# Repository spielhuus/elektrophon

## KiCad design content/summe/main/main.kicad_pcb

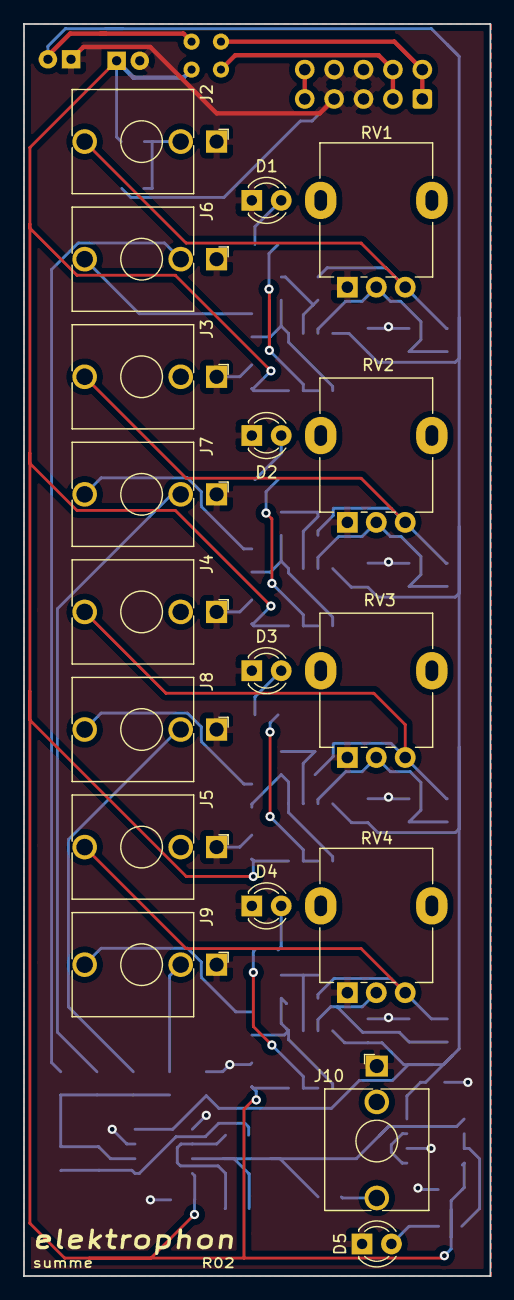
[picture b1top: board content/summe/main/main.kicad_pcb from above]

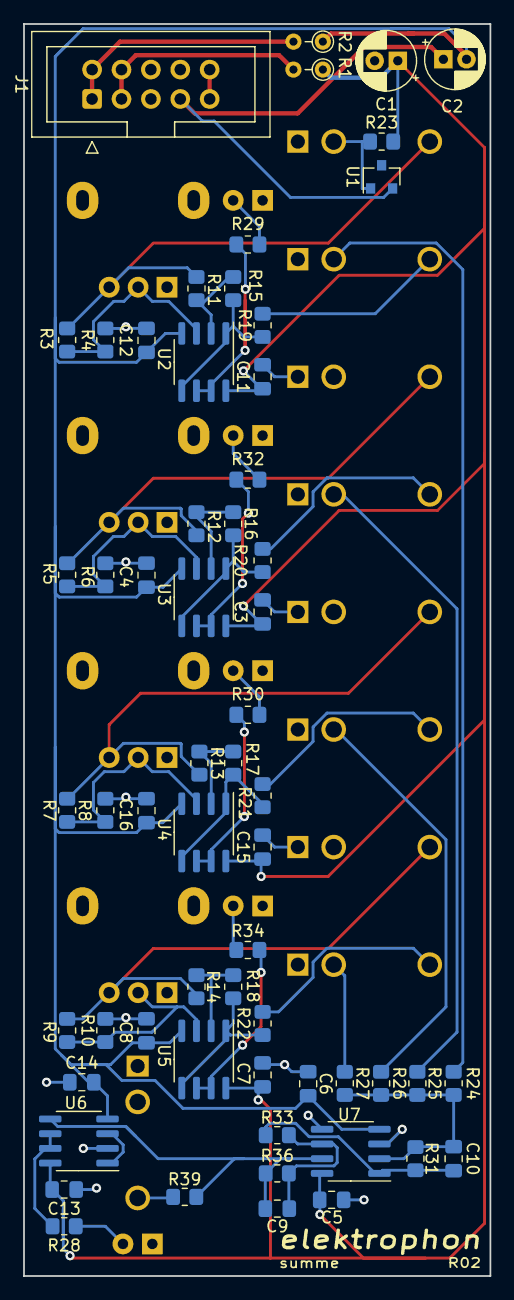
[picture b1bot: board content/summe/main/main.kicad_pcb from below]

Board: 2 copper layers, 40.3 x 108.2 mm, 78 parts (60 on the bottom side), 47 nets.

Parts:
C1, C2: 22u; CP_Radial_D5.0mm_P2.00mm
C3, C4, C5, C6, C7, C8, C11, C12, C13, C14, C15, C16: 0.1u; C_0805_2012Metric_Pad1.18x1.45mm_HandSolder
C9, C10: 100p; C_0805_2012Metric_Pad1.18x1.45mm_HandSolder
D1, D2, D3, D4: LED (Green/Yellow); LED_D3.0mm
D5: LED (Red/Yellow); LED_D3.0mm
J1: IDC Header; IDC-Header_2x05_P2.54mm_Vertical
J2, J3, J4, J5: IN; Jack_3.5mm_WQP-PJ398SM_Vertical
J6, J7, J8, J9, J10: OUT; Jack_3.5mm_WQP-PJ398SM_Vertical
R1, R2: 10; R_Axial_DIN0204_L3.6mm_D1.6mm_P2.54mm_Vertical
R3, R4, R5, R6, R7, R8, R9, R10: 47k; R_0805_2012Metric_Pad1.20x1.40mm_HandSolder
R11, R12, R13, R14, R15, R16, R17, R18, R24, R25, R26, R27, R31, R33, R36: 100k; R_0805_2012Metric_Pad1.20x1.40mm_HandSolder
R19, R20, R21, R22, R39: 1k; R_0805_2012Metric_Pad1.20x1.40mm_HandSolder
R23: 8.2k; R_0805_2012Metric_Pad1.20x1.40mm_HandSolder
R28, R29, R30, R32, R34: 500; R_0805_2012Metric_Pad1.20x1.40mm_HandSolder
RV1, RV2, RV3, RV4: 100k; Potentiometer_Alpha_RD901F-40-00D_Single_Vertical
U1: LM4040BIM3-5.0; SOT-23
U2, U3, U4, U5, U6, U7: TL072; SOIC-8_3.9x4.9mm_P1.27mm

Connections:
+5V: J1.9, J1.10
+15V: C1.1, C3.1, C5.1, C7.1, C11.1, C13.1, C15.1, R1.1, R23.2, U2.8, U3.8, U4.8, U5.8, U6.8, U7.8
-15V: C2.2, C4.2, C6.2, C8.2, C12.2, C14.2, C16.2, R2.1, U2.4, U3.4, U4.4, U5.4, U6.4, U7.4
/IN_1: R15.1, R19.1, U2.1, U2.5
/IN_2: R16.1, R20.1, U3.1, U3.5
/IN_3: R17.1, R21.1, U4.1, U4.5
/IN_4: R18.1, R22.1, U5.1, U5.5
/MIX_1: J6.TN, R24.1
/MIX_2: J7.TN, R25.1
/MIX_3: J8.TN, R26.1
/MIX_4: J9.TN, R27.1
/OUT: C9.1, R36.2, R39.1, U6.5, U7.7
/REF: J2.TN, R23.1, U1.1
GND: C1.2, C2.1, C3.2, C4.1, C5.2, C6.1, C7.2, C8.1, C11.2, C12.1, C13.2, C14.1, C15.2, C16.1, D1.1, D2.1, D3.1, D4.1, D5.1, J1.5, J1.6, J1.7, J1.8, J2.S, J3.S, J4.S, J5.S, J6.S, J7.S, J8.S, J9.S, J10.S, R4.2, R6.2, R8.2, R10.2, RV1.1, RV2.1, RV3.1, RV4.1, U1.2, U6.2, U7.3, U7.5
unnamed: C9.2, R33.2, R36.1, U7.6
unnamed: C10.1, R31.2, R33.1, U7.1
unnamed: C10.2, R24.2, R25.2, R26.2, R27.2, R31.1, U7.2
unnamed: D1.2, R29.1
unnamed: D2.2, R32.1
unnamed: D3.2, R30.1
unnamed: D4.2, R34.1
unnamed: D5.2, R28.1
unnamed: J2.T, R3.1, R11.2, RV1.3
unnamed: J3.T, R5.1, R12.2, RV2.3
unnamed: J4.T, R7.1, R13.2, RV3.3
unnamed: J5.T, R9.1, R14.2, RV4.3
unnamed: J6.T, R19.2
unnamed: J7.T, R20.2
unnamed: J8.T, R21.2
unnamed: J9.T, R22.2
unnamed: J10.T, R39.2
unnamed: R3.2, R4.1, RV1.2, U2.3
unnamed: R5.2, R6.1, RV2.2, U3.3
unnamed: R7.2, R8.1, RV3.2, U4.3
unnamed: R9.2, R10.1, RV4.2, U5.3
unnamed: R11.1, R15.2, U2.2
unnamed: R12.1, R16.2, U3.2
unnamed: R13.1, R17.2, U4.2
unnamed: R14.1, R18.2, U5.2
unnamed: R28.2, U6.6, U6.7
unnamed: R29.2, U2.6, U2.7
unnamed: R30.2, U4.6, U4.7
unnamed: R32.2, U3.6, U3.7
unnamed: R34.2, U5.6, U5.7
unnamed: U6.1, U6.3
VN: J1.1, J1.2, R2.2
VP: J1.3, J1.4, R1.2

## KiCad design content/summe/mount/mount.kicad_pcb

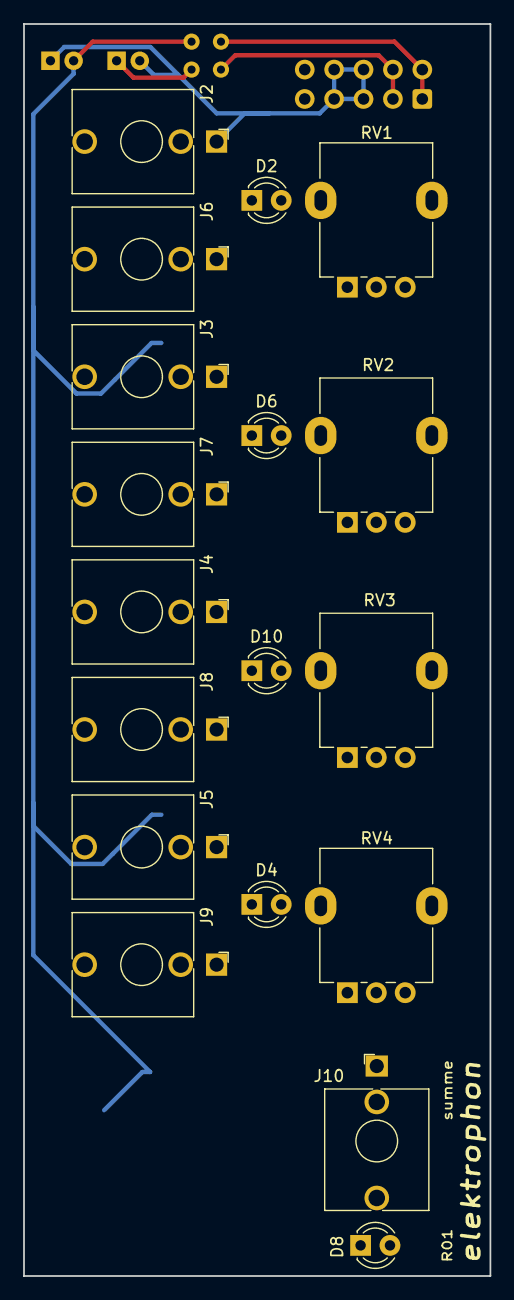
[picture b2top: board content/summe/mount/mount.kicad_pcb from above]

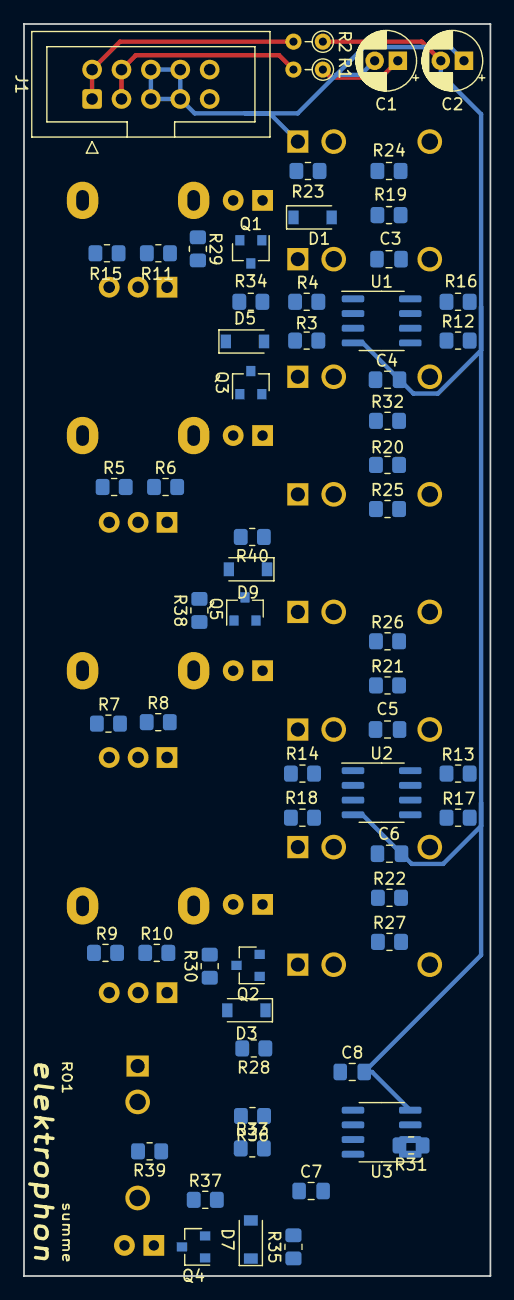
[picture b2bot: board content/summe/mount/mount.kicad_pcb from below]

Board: 2 copper layers, 40.3 x 108.2 mm, 80 parts (62 on the bottom side), 50 nets.

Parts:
C1, C2: 22u; CP_Radial_D5.0mm_P2.00mm
C3, C4, C5, C6, C7, C8: 0.1u; C_0805_2012Metric_Pad1.18x1.45mm_HandSolder
D1, D3, D5, D7, D9: 1N4148W; D_SOD-123
D2, D4, D6, D8, D10: LED; LED_D3.0mm
J1: IDC Header; IDC-Header_2x05_P2.54mm_Vertical
J2, J3, J4, J5: IN; Jack_3.5mm_WQP-PJ398SM_Vertical
J6, J7, J8, J9, J10: OUT; Jack_3.5mm_WQP-PJ398SM_Vertical
Q1, Q2, Q3, Q4, Q5: MMBT3904; SOT-23
R1, R2: 10; R_Axial_DIN0204_L3.6mm_D1.6mm_P2.54mm_Vertical
R3, R4, R5, R6, R7, R8, R9, R10: 47k; R_0805_2012Metric_Pad1.20x1.40mm_HandSolder
R11, R12, R13, R14, R15, R16, R17, R18, R23, R24, R25, R26, R27, R28, R31, R32, R33, R35, R36, R38: 100k; R_0805_2012Metric_Pad1.20x1.40mm_HandSolder
R19, R20, R21, R22, R39: 1k; R_0805_2012Metric_Pad1.20x1.40mm_HandSolder
R29, R30, R34, R37, R40: 5k; R_0805_2012Metric_Pad1.20x1.40mm_HandSolder
RV1, RV2, RV3, RV4: 100k; Potentiometer_Alpha_RD901F-40-00D_Single_Vertical
U1, U2, U3: OPA2134; SOIC-8_3.9x4.9mm_P1.27mm

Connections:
+5V: J1.9, J1.10, R29.1, R30.1, R34.1, R37.1, R40.1
+15V: C1.1, C3.1, C5.1, C7.1, R1.1, U1.8, U2.8, U3.8
-15V: C2.2, C4.2, C6.2, C8.2, R2.1, U1.4, U2.4, U3.4
/IN_1: J2.T, R3.1, R11.2, R23.2, RV1.3
/IN_2: J3.T, R5.1, R12.2, R32.2, RV2.3
/IN_3: J4.T, R7.1, R13.2, R38.2, RV3.3
/IN_4: J5.T, R9.1, R14.2, R28.2, RV4.3
/MIX_1: J6.TN, R24.1
/MIX_2: J7.TN, R25.1
/MIX_3: J8.TN, R26.1
/MIX_4: J9.TN, R27.1
/OUT: R35.2, R36.2, R39.1, U3.7
GND: C1.2, C2.1, C3.2, C4.1, C5.2, C6.1, C7.2, C8.1, D1.2, D2.1, D3.2, D4.1, D5.2, D6.1, D7.2, D8.1, D9.2, D10.1, J1.5, J1.6, J1.7, J1.8, J2.S, J3.S, J4.S, J5.S, J6.S, J7.S, J8.S, J9.S, J10.S, R4.2, R6.2, R8.2, R10.2, RV1.1, RV2.1, RV3.1, RV4.1, U3.3, U3.5
unnamed: D1.1, Q1.1, R23.1
unnamed: D2.2, Q1.2
unnamed: D3.1, Q2.1, R28.1
unnamed: D4.2, Q2.2
unnamed: D5.1, Q3.1, R32.1
unnamed: D6.2, Q3.2
unnamed: D7.1, Q4.1, R35.1
unnamed: D8.2, Q4.2
unnamed: D9.1, Q5.1, R38.1
unnamed: D10.2, Q5.2
unnamed: J6.T, R19.2
unnamed: J7.T, R20.2
unnamed: J8.T, R21.2
unnamed: J9.T, R22.2
unnamed: J10.T, R39.2
unnamed: Q1.3, R29.2
unnamed: Q2.3, R30.2
unnamed: Q3.3, R34.2
unnamed: Q4.3, R37.2
unnamed: Q5.3, R40.2
unnamed: R3.2, R4.1, RV1.2, U1.3
unnamed: R5.2, R6.1, RV2.2, U1.5
unnamed: R7.2, R8.1, RV3.2, U2.3
unnamed: R9.2, R10.1, RV4.2, U2.5
unnamed: R11.1, R15.2, U1.2
unnamed: R12.1, R16.2, U1.6
unnamed: R13.1, R17.2, U2.2
unnamed: R14.1, R18.2, U2.6
unnamed: R15.1, R19.1, U1.1
unnamed: R16.1, R20.1, U1.7
unnamed: R17.1, R21.1, U2.1
unnamed: R18.1, R22.1, U2.7
unnamed: R24.2, R25.2, R26.2, R27.2, R31.1, U3.2
unnamed: R31.2, R33.1, U3.1
unnamed: R33.2, R36.1, U3.6
VN: J1.1, J1.2, R2.2
VP: J1.3, J1.4, R1.2

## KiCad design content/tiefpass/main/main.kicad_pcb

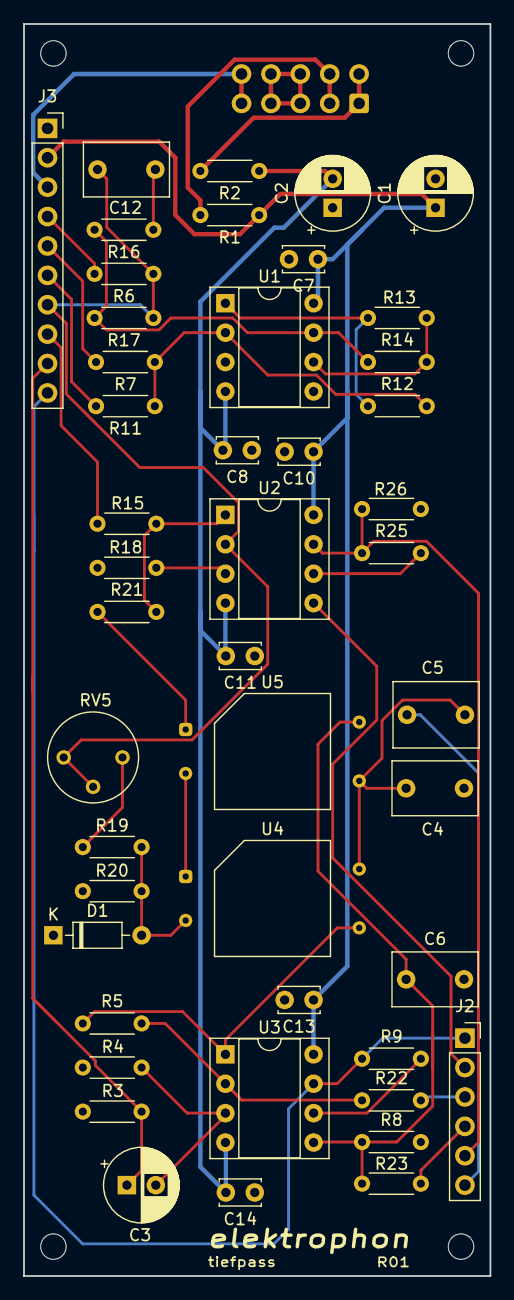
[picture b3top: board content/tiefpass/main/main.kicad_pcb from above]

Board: 2 copper layers, 40.3 x 108.2 mm, 51 parts (1 on the bottom side), 36 nets.

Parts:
C1, C2: 22u; CP_Radial_D6.3mm_P2.50mm
C3: 1u; CP_Radial_D6.3mm_P2.50mm
C4: 220p; C_Rect_L7.2mm_W4.5mm_P5.00mm_FKS2_FKP2_MKS2_MKP2
C5: 4.7n; C_Rect_L7.2mm_W5.5mm_P5.00mm_FKS2_FKP2_MKS2_MKP2
C6: 1n; C_Rect_L7.2mm_W4.5mm_P5.00mm_FKS2_FKP2_MKS2_MKP2
C7, C8, C10, C11, C13, C14: 0.1u; C_Disc_D3.4mm_W2.1mm_P2.50mm
C12: 2.2n; C_Rect_L7.2mm_W4.5mm_P5.00mm_FKS2_FKP2_MKS2_MKP2
D1: 3.9V; D_DO-35_SOD27_P7.62mm_Horizontal
H1, H2, H3, H4: MountingHole; MountingHole_2.2mm_M2
J1: 10 Pos; IDC-Header_2x05_P2.54mm_Vertical
J2: 01x06 Female; PinSocket_1x06_P2.54mm_Vertical
J3: 01x10 Female; PinSocket_1x10_P2.54mm_Vertical
R1, R2: 10; R_Axial_DIN0204_L3.6mm_D1.6mm_P5.08mm_Horizontal
R3, R4, R7, R11, R12, R13, R14, R17, R20: 100k; R_Axial_DIN0204_L3.6mm_D1.6mm_P5.08mm_Horizontal
R5, R22: 15k; R_Axial_DIN0204_L3.6mm_D1.6mm_P5.08mm_Horizontal
R6: 150k; R_Axial_DIN0204_L3.6mm_D1.6mm_P5.08mm_Horizontal
R8: 4.7M; R_Axial_DIN0204_L3.6mm_D1.6mm_P5.08mm_Horizontal
R9, R18, R23, R25, R26: 10k; R_Axial_DIN0204_L3.6mm_D1.6mm_P5.08mm_Horizontal
R15, R21: 470; R_Axial_DIN0204_L3.6mm_D1.6mm_P5.08mm_Horizontal
R16: 470k; R_Axial_DIN0204_L3.6mm_D1.6mm_P5.08mm_Horizontal
R19: 33k; R_Axial_DIN0204_L3.6mm_D1.6mm_P5.08mm_Horizontal
RV5: 20k; Potentiometer_Bourns_3339P_Vertical
U1, U2, U3: TL072; DIP-8_W7.62mm_Socket
U4, U5: VTL5C; PerkinElmer_VTL5C

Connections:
+5V: J1.9, J1.10, J3.3
+15V: C1.1, C7.1, C10.1, C13.1, J3.2, R1.1, U1.8, U2.8, U3.8
-15V: C2.2, C8.2, C11.2, C14.2, R2.1, U1.4, U2.4, U3.4
/S1: J2.3, R22.2
/S2: J2.4, R23.2
/S2a: C12.1, J3.7, R6.1, R17.1, RV5.2, RV5.3, U2.2
/S2b: J3.8, R15.2
/S3: J2.5, R25.1, R26.2, U2.7
/S4: C5.2, J2.6
CV: J3.4, R6.2
CV1: J3.5, R7.2
CV2: J3.6, R11.2
GND: C1.2, C2.1, C4.2, C6.2, C7.2, C8.1, C10.2, C11.1, C13.2, C14.1, D1.1, J1.5, J1.6, J1.7, J1.8, J3.1, R3.2, R4.2, R8.2, R18.2, R20.1, R26.1, U1.3, U1.5
IN: C3.1, J3.9, R3.1
unnamed: C3.2, R4.1, U3.3
unnamed: C4.1, C5.1, U4.3, U5.4
unnamed: C6.1, R8.1, R23.1, U3.5, U5.3
unnamed: C12.2, R16.1
unnamed: D1.2, R19.1, R20.2, U4.2
unnamed: R5.1, U3.1, U4.4
unnamed: R9.2, U3.6
unnamed: R7.1, R11.1, R12.2, U1.2
unnamed: R12.1, R13.2, U1.1
unnamed: R13.1, R14.2, U1.6
unnamed: R14.1, R16.2, R17.2, U1.7
unnamed: R15.1, R21.2, U2.1
unnamed: R18.1, U2.3
unnamed: R19.2, RV5.1
unnamed: R21.1, U5.1
unnamed: R5.2, R22.1, U3.2
unnamed: R25.2, U2.6
unnamed: U4.1, U5.2
OUT: J2.1, J3.10, R9.1, U3.7
RES_1_out: J2.2, U2.5
VN: J1.1, J1.2, R2.2
VP: J1.3, J1.4, R1.2

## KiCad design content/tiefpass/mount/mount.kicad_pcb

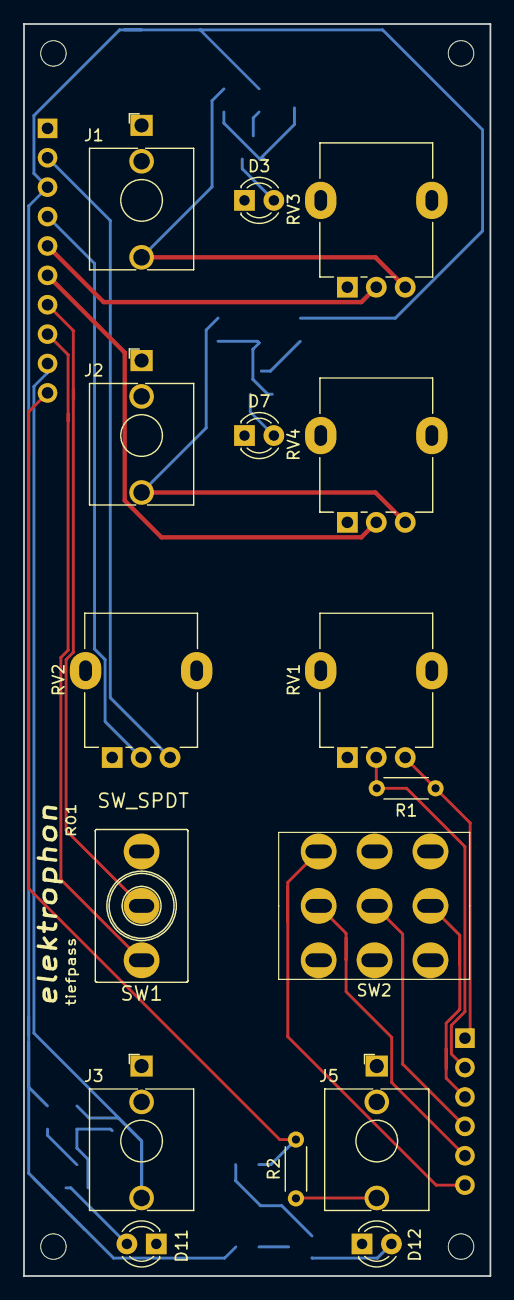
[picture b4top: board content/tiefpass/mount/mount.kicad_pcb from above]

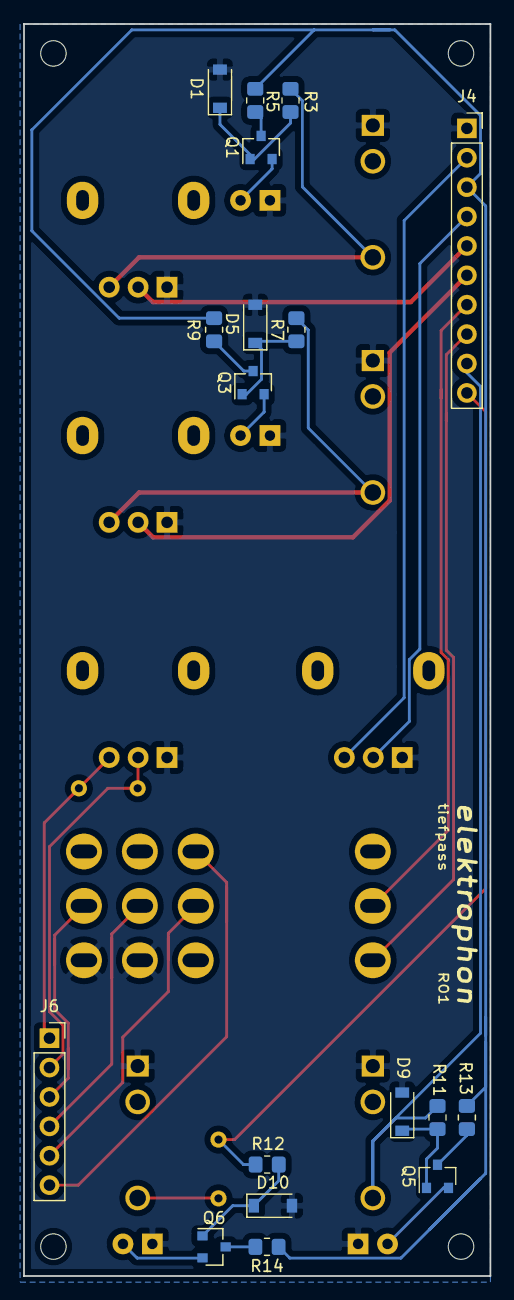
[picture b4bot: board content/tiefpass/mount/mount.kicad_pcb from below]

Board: 2 copper layers, 40.3 x 108.2 mm, 38 parts (18 on the bottom side), 31 nets.

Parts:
D1, D5, D9, D10: 1N4148W; D_SOD-123
D3, D7: LED (Yellow); LED_D3.0mm
D11: LED (Green); LED_D3.0mm
D12: LED (Red); LED_D3.0mm
H1, H2, H3, H4: MountingHole; MountingHole_2.2mm_M2
J1: CV1; Jack_3.5mm_WQP-PJ398SM_Vertical
J2: CV2; Jack_3.5mm_WQP-PJ398SM_Vertical
J3: IN; Jack_3.5mm_WQP-PJ398SM_Vertical
J4: Conn_01x10_Male; PinSocket_1x10_P2.54mm_Vertical
J5: OUT; Jack_3.5mm_WQP-PJ398SM_Vertical
J6: Conn_01x06_Male; PinSocket_1x06_P2.54mm_Vertical
Q1, Q3, Q5, Q6: MMBT3904; SOT-23
R1: 22k; R_Axial_DIN0204_L3.6mm_D1.6mm_P5.08mm_Horizontal
R2: 1k; R_Axial_DIN0204_L3.6mm_D1.6mm_P5.08mm_Horizontal
R3, R7, R11, R12: 100k; R_0805_2012Metric_Pad1.20x1.40mm_HandSolder
R5, R9, R13, R14: 5k; R_0805_2012Metric_Pad1.20x1.40mm_HandSolder
RV1, RV3, RV4: 100k; Potentiometer_Alpha_RD901F-40-00D_Single_Vertical
RV2: 10k; Potentiometer_Alpha_RD901F-40-00D_Single_Vertical
SW1: SW_SPDT; SPDT_KIT
SW2: SWITCH_3PDT; 3PDT

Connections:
+5V: J4.3, R5.1, R9.1, R13.1, R14.1
+15V: J4.2, RV2.3
/CV_1: J1.T, R3.2, RV3.3
/CV_2: J2.T, R7.2, RV4.3
/S1: J6.3, SW2.2
/S2: J6.4, SW2.5
/S2a: J4.7, SW1.2
/S2b: J4.8, SW1.1
/S3: J6.5, SW2.8
/S4: J6.6, SW2.9
CV: J4.4, RV2.2
CV1: J4.5, RV3.2
CV2: J4.6, RV4.2
GND: D1.2, D3.1, D5.2, D7.1, D9.2, D10.2, D11.1, D12.1, J1.S, J2.S, J3.S, J4.1, J5.S, RV1.1, RV2.1, RV3.1, RV4.1, SW2.1, SW2.4
IN: J3.T, J4.9, R11.2
unnamed: D1.1, Q1.1, R3.1
unnamed: D3.2, Q1.2
unnamed: D5.1, Q3.1, R7.1
unnamed: D7.2, Q3.2
unnamed: D9.1, Q5.1, R11.1
unnamed: D10.1, Q6.1, R12.1
unnamed: D11.2, Q5.2
unnamed: D12.2, Q6.2
unnamed: J5.T, R2.1
unnamed: Q1.3, R5.2
unnamed: Q3.3, R9.2
unnamed: Q5.3, R13.2
unnamed: Q6.3, R14.2
OUT: J4.10, R2.2, R12.2
RES_1: J6.1, R1.1, RV1.3
RES_1_out: J6.2, R1.2, RV1.2

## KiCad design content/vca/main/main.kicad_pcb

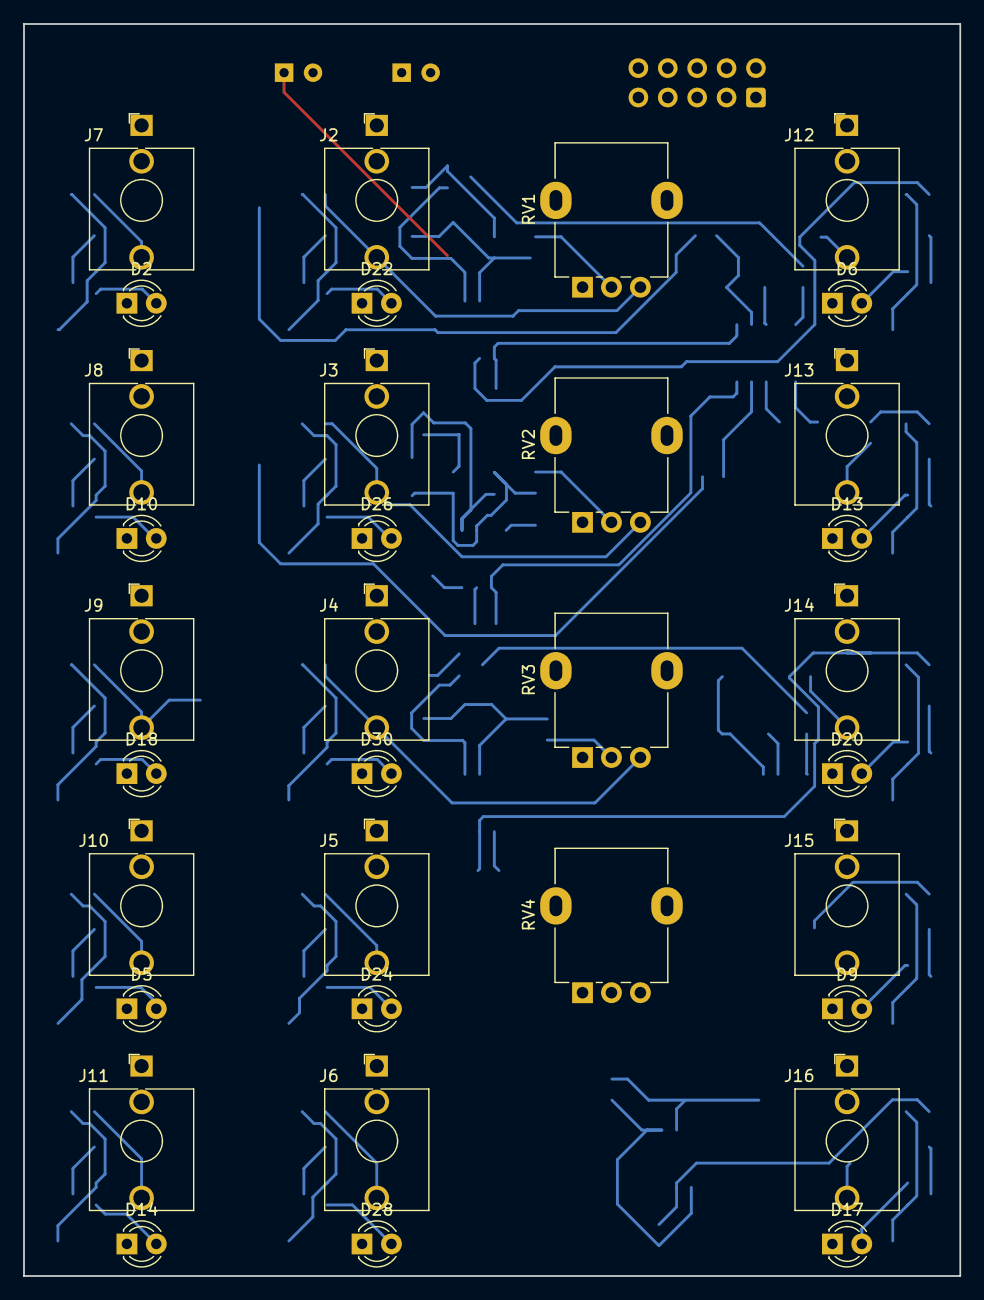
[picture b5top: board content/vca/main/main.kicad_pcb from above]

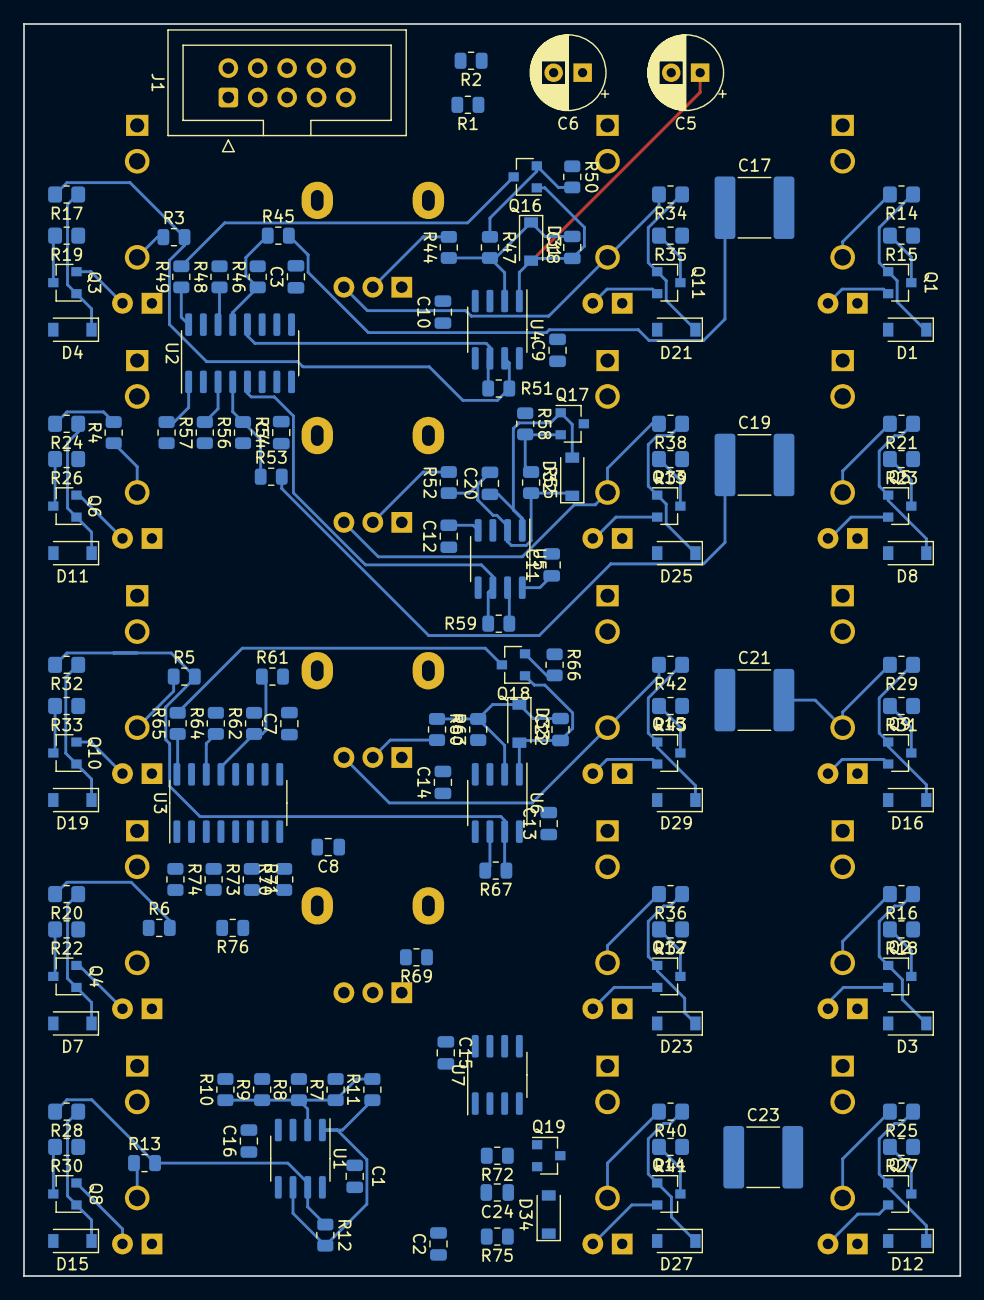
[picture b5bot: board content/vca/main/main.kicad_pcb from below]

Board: 2 copper layers, 80.9 x 108.2 mm, 179 parts (145 on the bottom side), 116 nets.

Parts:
C1, C2, C3, C4, C7, C8, C9, C10, C11, C12, C13, C14, C15, C16: 0.1u; C_0805_2012Metric
C5, C6: 22u; CP_Radial_D6.3mm_P2.50mm
C17, C19, C21, C23: 470n; C_2220_5650Metric
C18, C20, C22, C24: 1n; C_0805_2012Metric
D1, D3, D4, D7, D8, D11, D12, D15, D16, D19, D21, D23, D25, D27, D29, D31, D32, D33, D34: 1N4148W; D_SOD-123
D2, D5, D6, D9, D10, D13, D14, D17, D18, D20, D22, D24, D26, D28, D30: LED; LED_D3.0mm
J1: IDC Header; IDC-Header_2x05_P2.54mm_Vertical
J2, J3, J4, J5, J6, J7, J8, J9, J10, J11, J12, J13, J14, J15, J16: AudioJack2_SwitchT; Jack_3.5mm_WQP-PJ398SM_Vertical
Q1, Q2, Q3, Q4, Q5, Q6, Q7, Q8, Q9, Q10, Q11, Q12, Q13, Q14, Q15: MMBT3904; SOT-23
Q16, Q17, Q18, Q19: MMBT3906; SOT-23
R1, R2: 10; R_0805_2012Metric
R3, R4, R5, R6, R13, R50, R58, R66, R75: 1k; R_0805_2012Metric
R7, R8, R9, R10, R11, R12, R45, R53, R61, R70: 100k; R_0805_2012Metric
R14, R16, R17, R20, R21, R24, R25, R28, R29, R32, R34, R36, R38, R40, R42: 100k; R_0805_2012Metric_Pad1.20x1.40mm_HandSolder
R15, R19, R23, R26, R31, R33, R35, R39, R43: 5.1k; R_0805_2012Metric_Pad1.20x1.40mm_HandSolder
R18, R22, R27, R30, R37, R41: 5k; R_0805_2012Metric_Pad1.20x1.40mm_HandSolder
R44, R52, R60, R69: 330k; R_0805_2012Metric
R46, R48, R54, R56, R62, R64, R71, R73: 620; R_0805_2012Metric
R47, R55, R63, R72: 33k; R_0805_2012Metric
R49, R57, R65, R74: 6.8k; R_0805_2012Metric
R51, R59, R67, R76: 18k; R_0805_2012Metric
RV1, RV2, RV3, RV4: R_POT; Potentiometer_Alpha_RD901F-40-00D_Single_Vertical
U1, U4, U5, U6, U7: TL072; SOIC-8_3.9x4.9mm_P1.27mm
U2, U3: LM13700; SOIC-16_3.9x9.9mm_P1.27mm

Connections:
+5V: J1.9, J1.10, R15.1, R18.1, R19.1, R22.1, R23.1, R26.1, R27.1, R30.1, R31.1, R33.1, R35.1, R37.1, R39.1, R41.1, R43.1
+15V: C1.1, C3.1, C5.1, C7.1, C9.1, C11.1, C13.1, C15.1, R1.1, U1.8, U2.11, U3.11, U4.8, U5.8, U6.8, U7.8
-15V: C2.2, C4.2, C6.2, C8.2, C10.2, C12.2, C14.2, C16.2, R2.1, U1.4, U2.6, U3.6, U4.4, U5.4, U6.4, U7.4
/CV_1: J2.T, R34.2, RV1.3
/CV_2: J3.T, R38.2, RV2.3
/CV_3: J4.T, R42.2, RV3.3
/CV_4: J5.T, R36.2, RV4.3
/CV_5: J2.TN, J3.TN, J4.TN, J5.TN, J6.T, R40.2
/IN_1: C17.2, J7.T, R14.2
/IN_2: C19.2, J8.T, R21.2
/IN_3: C21.2, J9.T, R29.2
/IN_4: C23.2, J7.TN, J8.TN, J9.TN, J10.T, J10.TN, J11.T, R16.2, R25.2
/MIX_1: J12.TN, R10.2
/MIX_2: J13.TN, R9.2
/MIX_3: J14.TN, R8.2
/MIX_4: J15.TN, R7.2
/OUT_1: R3.2, R17.2, R51.1, U4.7
/OUT_2: R4.2, R24.2, R59.1, U5.7
/OUT_3: R5.2, R32.2, R67.1, U6.7
/OUT_4: R6.2, R20.2, R76.1, U7.7
/OUT_5: R12.1, R13.2, R28.2, U1.7
/VCA1/CV_1: R44.2, RV1.2
/VCA2/CV_2: R52.2, RV2.2
/VCA3/CV_3: R60.2, RV3.2
/VCA4/CV_4: R69.2, RV4.2
GND: C1.2, C2.1, C3.2, C4.1, C5.2, C6.1, C7.2, C8.1, C9.2, C10.1, C11.2, C12.1, C13.2, C14.1, C15.2, C16.1, D1.2, D2.1, D3.2, D4.2, D5.1, D6.1, D7.2, D8.2, D9.1, D10.1, D11.2, D12.2, D13.1, D14.1, D15.2, D16.2, D17.1, D18.1, D19.2, D20.1, D21.2, D22.1, D23.2, D24.1, D25.2, D26.1, D27.2, D28.1, D29.2, D30.1, J1.5, J1.6, J1.7, J1.8, J2.S, J3.S, J4.S, J5.S, J6.S, J7.S, J8.S, J9.S, J10.S, J11.S, J12.S, J13.S, J14.S, J15.S, J16.S, R46.2, R48.2, R50.1, R54.2, R56.2, R58.1, R62.2, R64.2, R66.1, R71.2, R73.2, R75.1, RV1.1, RV2.1, RV3.1, RV4.1, U1.3, U1.5, U4.3, U4.5, U5.3, U5.5, U6.3, U6.5, U7.3, U7.5
unnamed: C17.1, R45.2
unnamed: C18.1, D31.2, Q16.1, U4.1
unnamed: C18.2, D31.1, R44.1, R47.2, U4.2
unnamed: C19.1, R53.2
unnamed: C20.1, D32.2, Q17.1, U5.1
unnamed: C20.2, D32.1, R52.1, R55.2, U5.2
unnamed: C21.1, R61.2
unnamed: C22.1, D33.2, Q18.1, U6.1
unnamed: C22.2, D33.1, R60.1, R63.2, U6.2
unnamed: C23.1, R70.2
unnamed: C24.1, D34.2, Q19.1, U7.1
unnamed: C24.2, D34.1, R69.1, R72.2, U7.2
unnamed: D1.1, Q1.1, R14.1
unnamed: D2.2, Q1.2
unnamed: D3.1, Q2.1, R16.1
unnamed: D4.1, Q3.1, R17.1
unnamed: D5.2, Q2.2
unnamed: D6.2, Q3.2
unnamed: D7.1, Q4.1, R20.1
unnamed: D8.1, Q5.1, R21.1
unnamed: D9.2, Q4.2
unnamed: D10.2, Q5.2
unnamed: D11.1, Q6.1, R24.1
unnamed: D12.1, Q7.1, R25.1
unnamed: D13.2, Q6.2
unnamed: D14.2, Q7.2
unnamed: D15.1, Q8.1, R28.1
unnamed: D16.1, Q9.1, R29.1
unnamed: D17.2, Q8.2
unnamed: D18.2, Q9.2
unnamed: D19.1, Q10.1, R32.1
unnamed: D20.2, Q10.2
unnamed: D21.1, Q11.1, R34.1
unnamed: D22.2, Q11.2
unnamed: D23.1, Q12.1, R36.1
unnamed: D24.2, Q12.2
unnamed: D25.1, Q13.1, R38.1
unnamed: D26.2, Q13.2
unnamed: D27.1, Q14.1, R40.1
unnamed: D28.2, Q14.2
unnamed: D29.1, Q15.1, R42.1
unnamed: D30.2, Q15.2
unnamed: J12.T, R3.1
unnamed: J13.T, R4.1
unnamed: J14.T, R5.1
unnamed: J15.T, R6.1
unnamed: J16.T, R13.1
unnamed: Q1.3, R15.2
unnamed: Q2.3, R18.2
unnamed: Q3.3, R19.2
unnamed: Q4.3, R22.2
unnamed: Q5.3, R23.2
unnamed: Q6.3, R26.2
unnamed: Q7.3, R27.2
unnamed: Q8.3, R30.2
unnamed: Q9.3, R31.2
unnamed: Q10.3, R33.2
unnamed: Q11.3, R35.2
unnamed: Q12.3, R37.2
unnamed: Q13.3, R39.2
unnamed: Q14.3, R41.2
unnamed: Q15.3, R43.2
unnamed: Q16.2, R47.1, R50.2
unnamed: Q16.3, R49.2
unnamed: Q17.2, R55.1, R58.2
unnamed: Q17.3, R57.2
unnamed: Q18.2, R63.1, R66.2
unnamed: Q18.3, R65.2
unnamed: Q19.2, R72.1, R75.2
unnamed: Q19.3, R74.2
unnamed: R7.1, R8.1, R9.1, R10.1, R11.2, U1.2
unnamed: R11.1, R12.2, U1.1, U1.6
unnamed: R45.1, R46.1, U2.13
unnamed: R48.1, U2.14
unnamed: R49.1, U2.16
unnamed: R51.2, U2.12, U4.6
unnamed: R53.1, R54.1, U2.4
unnamed: R56.1, U2.3
unnamed: R57.1, U2.1
unnamed: R59.2, U2.5, U5.6
unnamed: R61.1, R62.1, U3.13
unnamed: R64.1, U3.14
unnamed: R65.1, U3.16
unnamed: R67.2, U3.12, U6.6
unnamed: R70.1, R71.1, U3.4
unnamed: R73.1, U3.3
unnamed: R74.1, U3.1
unnamed: R76.2, U3.5, U7.6
VN: J1.1, J1.2, R2.2
VP: J1.3, J1.4, R1.2

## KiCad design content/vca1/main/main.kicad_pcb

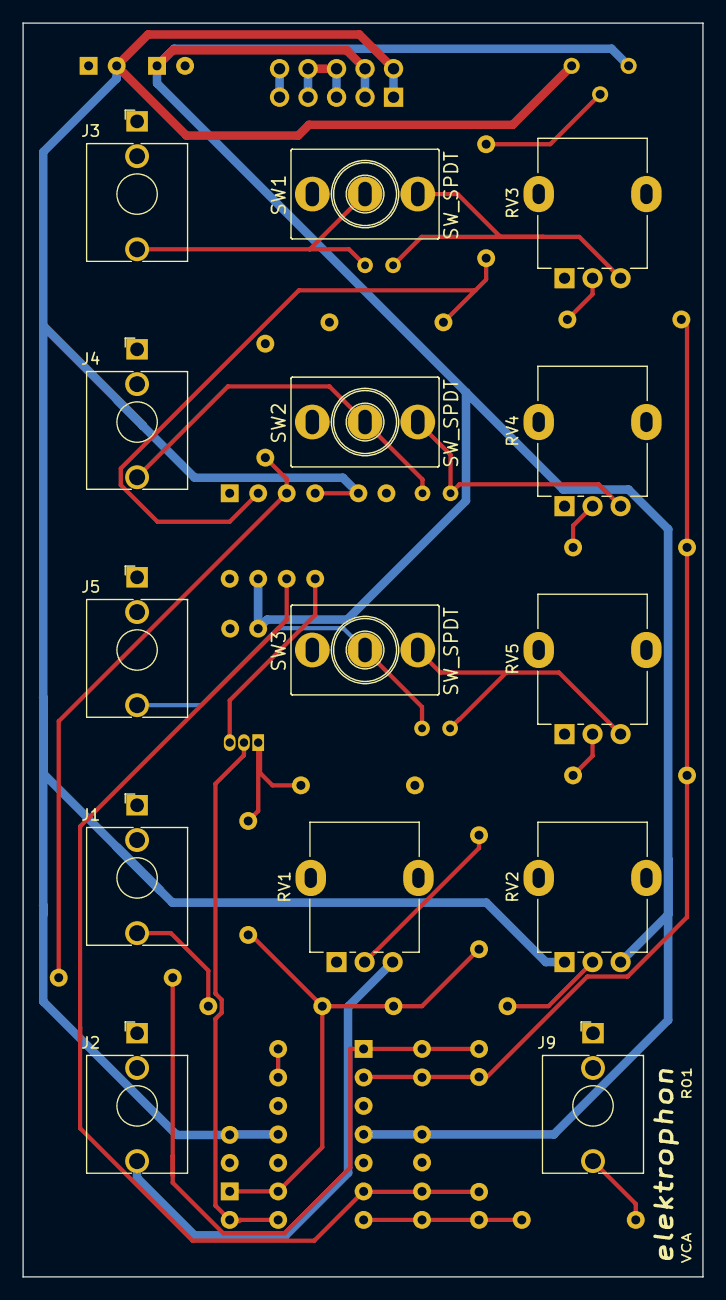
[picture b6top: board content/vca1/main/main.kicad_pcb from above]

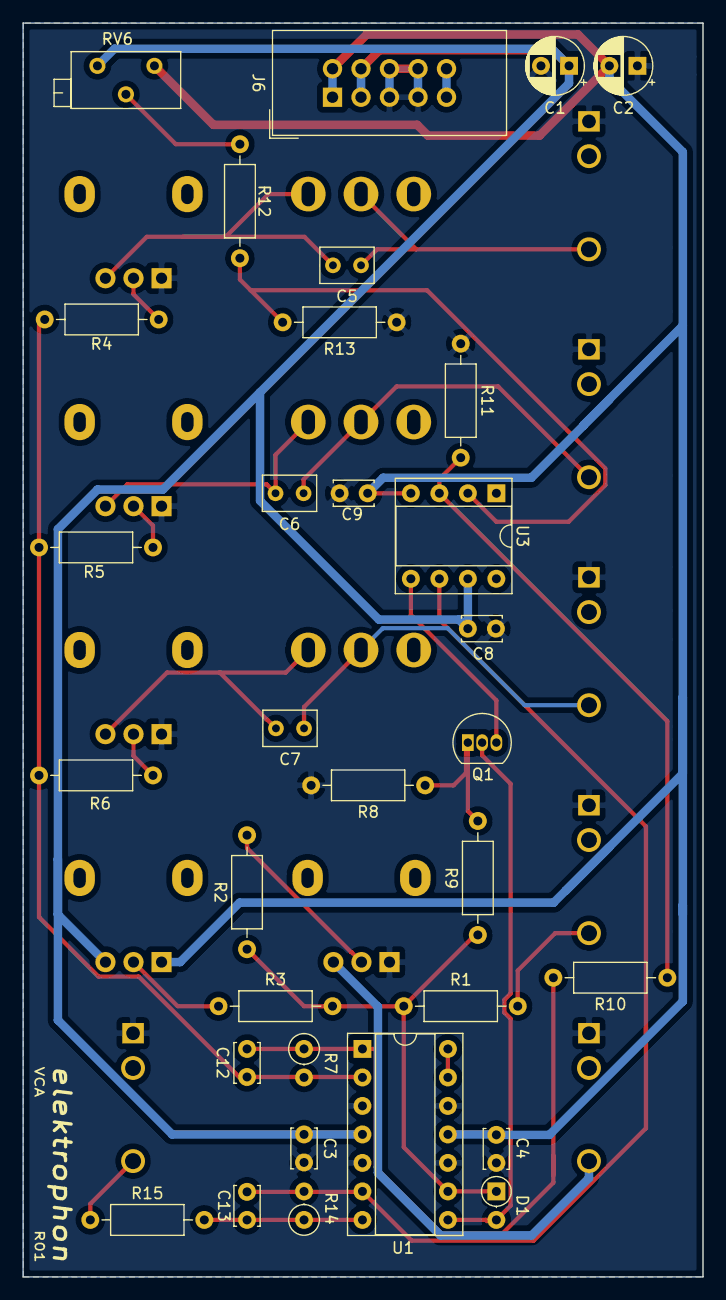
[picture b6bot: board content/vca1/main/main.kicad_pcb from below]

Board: 2 copper layers, 60.6 x 111.8 mm, 46 parts (32 on the bottom side), 30 nets.

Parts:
C1, C2: 10u; CP_Radial_D5.0mm_P2.50mm
C3, C4, C8, C9: 0.1u; C_Disc_D3.4mm_W2.1mm_P2.50mm
C5, C6, C7: 0.22u; C_Rect_L4.6mm_W3.0mm_P2.50mm_MKS02_FKP02
C12: 10p; C_Disc_D3.4mm_W2.1mm_P2.50mm
C13: 22p; C_Disc_D3.4mm_W2.1mm_P2.50mm
D1: 1N4148; D_DO-35_SOD27_P2.54mm_Vertical_AnodeUp
J1: Envelope; Jack_3.5mm_QingPu_WQP-PJ398SM_Vertical_CircularHoles
J2: CV; Jack_3.5mm_QingPu_WQP-PJ398SM_Vertical_CircularHoles
J3: #1; Jack_3.5mm_QingPu_WQP-PJ398SM_Vertical_CircularHoles
J4: #2; Jack_3.5mm_QingPu_WQP-PJ398SM_Vertical_CircularHoles
J5: #3; Jack_3.5mm_QingPu_WQP-PJ398SM_Vertical_CircularHoles
J6: POWER; IDC-Header_2x05_P2.54mm_Vertical
J9: OUT; Jack_3.5mm_QingPu_WQP-PJ398SM_Vertical_CircularHoles
Q1: 2N3906; TO-92_Inline
R1, R2, R4, R5, R6, R9, R12: 100k; R_Axial_DIN0207_L6.3mm_D2.5mm_P10.16mm_Horizontal
R3: 330k; R_Axial_DIN0207_L6.3mm_D2.5mm_P10.16mm_Horizontal
R7: 100k; R_Axial_DIN0207_L6.3mm_D2.5mm_P2.54mm_Vertical
R8, R10: 11k; R_Axial_DIN0207_L6.3mm_D2.5mm_P10.16mm_Horizontal
R11, R13: 22; R_Axial_DIN0207_L6.3mm_D2.5mm_P10.16mm_Horizontal
R14: 51k; R_Axial_DIN0207_L6.3mm_D2.5mm_P2.54mm_Vertical
R15: 1k; R_Axial_DIN0207_L6.3mm_D2.5mm_P10.16mm_Horizontal
RV1, RV2, RV3, RV4, RV5: 100k; Potentiometer_Alpha_RD901F-40-00D_Single_Vertical
RV6: 100k; Potentiometer_Bourns_3296Z_Horizontal
SW1, SW2, SW3: SW_SPDT; SPDT_KIT
U1: TL074; DIP-14_W7.62mm_Socket
U3: CA3080; DIP-8_W7.62mm_Socket

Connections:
+5V: J6.9, J6.10
+15V: C1.1, C3.1, C8.1, J6.3, J6.4, RV2.3, RV6.3, U1.4, U3.7
-15V: C2.2, C4.2, C9.2, J6.1, J6.2, RV2.1, RV6.1, U1.11, U3.4
GND: C1.2, C2.1, C3.2, C4.1, C8.2, C9.1, J1.S, J2.S, J3.S, J4.S, J5.S, J6.5, J6.6, J6.7, J6.8, J9.S, R8.2, R11.1, R13.1, RV1.1, RV3.1, RV4.1, RV5.1, U1.3, U1.5, U1.10, U1.12
unnamed: C5.1, J3.T, SW1.2
unnamed: C5.2, RV3.3, SW1.3
unnamed: C6.1, J4.T, SW2.2
unnamed: C6.2, RV4.3, SW2.3
unnamed: C7.1, J5.T, SW3.2
unnamed: C7.2, RV5.3, SW3.3
unnamed: C12.1, R7.1, R10.2, U1.1
unnamed: C12.2, R4.1, R5.1, R6.1, R7.2, U1.2
unnamed: C13.1, R14.1, R15.2, U1.7
unnamed: C13.2, R14.2, U1.6, U3.6
unnamed: D1.1, R1.1, R2.1, R3.1, R9.1, U1.9
unnamed: D1.2, Q1.2, U1.8
unnamed: J1.T, R1.2
unnamed: J2.T, RV1.3
unnamed: J9.T, R15.1
unnamed: Q1.1, R8.1, R9.2
unnamed: Q1.3, U3.5
unnamed: R2.2, RV1.2
unnamed: R3.2, RV2.2
unnamed: R4.2, RV3.2
unnamed: R5.2, RV4.2
unnamed: R6.2, RV5.2
unnamed: R10.1, R11.2, U3.3
unnamed: R12.1, R13.2, U3.2
unnamed: R12.2, RV6.2
unnamed: U1.13, U1.14

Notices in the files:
content/summe/main/main.kicad_pcb:
License CC BY 4.0 - Attribution 4.0 International
